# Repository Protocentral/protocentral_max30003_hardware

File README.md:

# ProtoCentral MAX30003 Single-lead ECG Breakout — Hardware

Open-source hardware design files for the **ProtoCentral MAX30003 Single-lead ECG Breakout**, built around the [Analog Devices (Maxim) MAX30003](https://www.analog.com/en/products/max30003.html), an ultra-low-power single-channel biopotential AFE with built-in R-to-R (heart-rate) detection.

The board takes a single ECG lead from a standard 3.5 mm electrode cable. It runs the MAX30003 from an on-board 1.8 V rail and translates the SPI and interrupt lines to your host's logic level, so it connects directly to 3.3 V or 5 V microcontrollers.

## Links

| | |
|---|---|
| 🛒 Product page | https://protocentral.com/product/protocentral-max30003-single-lead-ecg-breakout-board-v2/ |
| 💻 Arduino library | https://github.com/Protocentral/protocentral_max30003 |
| 📄 IC datasheet (Analog Devices / Maxim) | https://www.analog.com/media/en/technical-documentation/data-sheets/max30003.pdf |

## Specifications (v3)

- **AFE:** MAX30003 single-channel ECG front end with R-to-R detection
- **Electrode input:** 3.5 mm jack (Tip = ECGN, Ring = ECGP, Sleeve = VCM), 49.9 kΩ series resistors and an RC EMI filter on each input
- **Interface:** SPI (`CSB`, `SCLK`, `MOSI`, `MISO`) plus `INTB` / `INT2B` interrupts, level-translated to host `VCC` by a TXB0108
- **Clock:** on-board SiT1533 32.768 kHz oscillator driving `FCLK`
- **Supply:** 3.3 V – 5 V on `VCC`; on-board AP2112K-1.8 LDO for the AFE
- **Host header (J2, 8-pin):** 1 `INTB` · 2 `INT2B` · 3 `MISO` · 4 `MOSI` · 5 `SCLK` · 6 `CSB` · 7 `VCC` · 8 `GND`
- **Board:** 33.0 × 28.6 mm, 2-layer

## Revisions

| Revision | Design files | Notes |
|---|---|---|
| **v3** (current) | [`hardware/`](hardware/) | KiCad 10 redesign; [schematic PDF](hardware/protocentral-max30003-v3-schematic.pdf) |
| v2.0 | [`hardware/previous-revisions/v2.0/`](hardware/previous-revisions/v2.0/) | Eagle (2018) |
| v1.1 | [`hardware/previous-revisions/v1.1/`](hardware/previous-revisions/v1.1/) | Eagle (2017) |
| v1.0 | [`hardware/previous-revisions/v1.0/`](hardware/previous-revisions/v1.0/) | Eagle (2017) |

The v2.0 files also remain in the original [protocentral_max30003](https://github.com/Protocentral/protocentral_max30003/tree/master/hardware) repository, so existing links keep working.

## Repository layout

| Folder | Contents |
|---|---|
| [`hardware/`](hardware/) | v3 KiCad project (schematic + PCB layout) and the exported [schematic PDF](hardware/protocentral-max30003-v3-schematic.pdf) |
| [`hardware/previous-revisions/`](hardware/previous-revisions/) | Eagle design files for v1.0, v1.1 and v2.0, kept for reference |

## Important notice

This device is intended for research, education, and evaluation use only. It is **not** a medical diagnostic instrument and is not FDA, CE, or FCC approved for consumer use.

## License

The hardware design files in this repository are licensed under the **CERN Open Hardware Licence Version 2 – Permissive (CERN-OHL-P v2)**. See [LICENSE](LICENSE).

The accompanying Arduino library (in the separate [protocentral_max30003](https://github.com/Protocentral/protocentral_max30003) repository) is licensed under the MIT License.

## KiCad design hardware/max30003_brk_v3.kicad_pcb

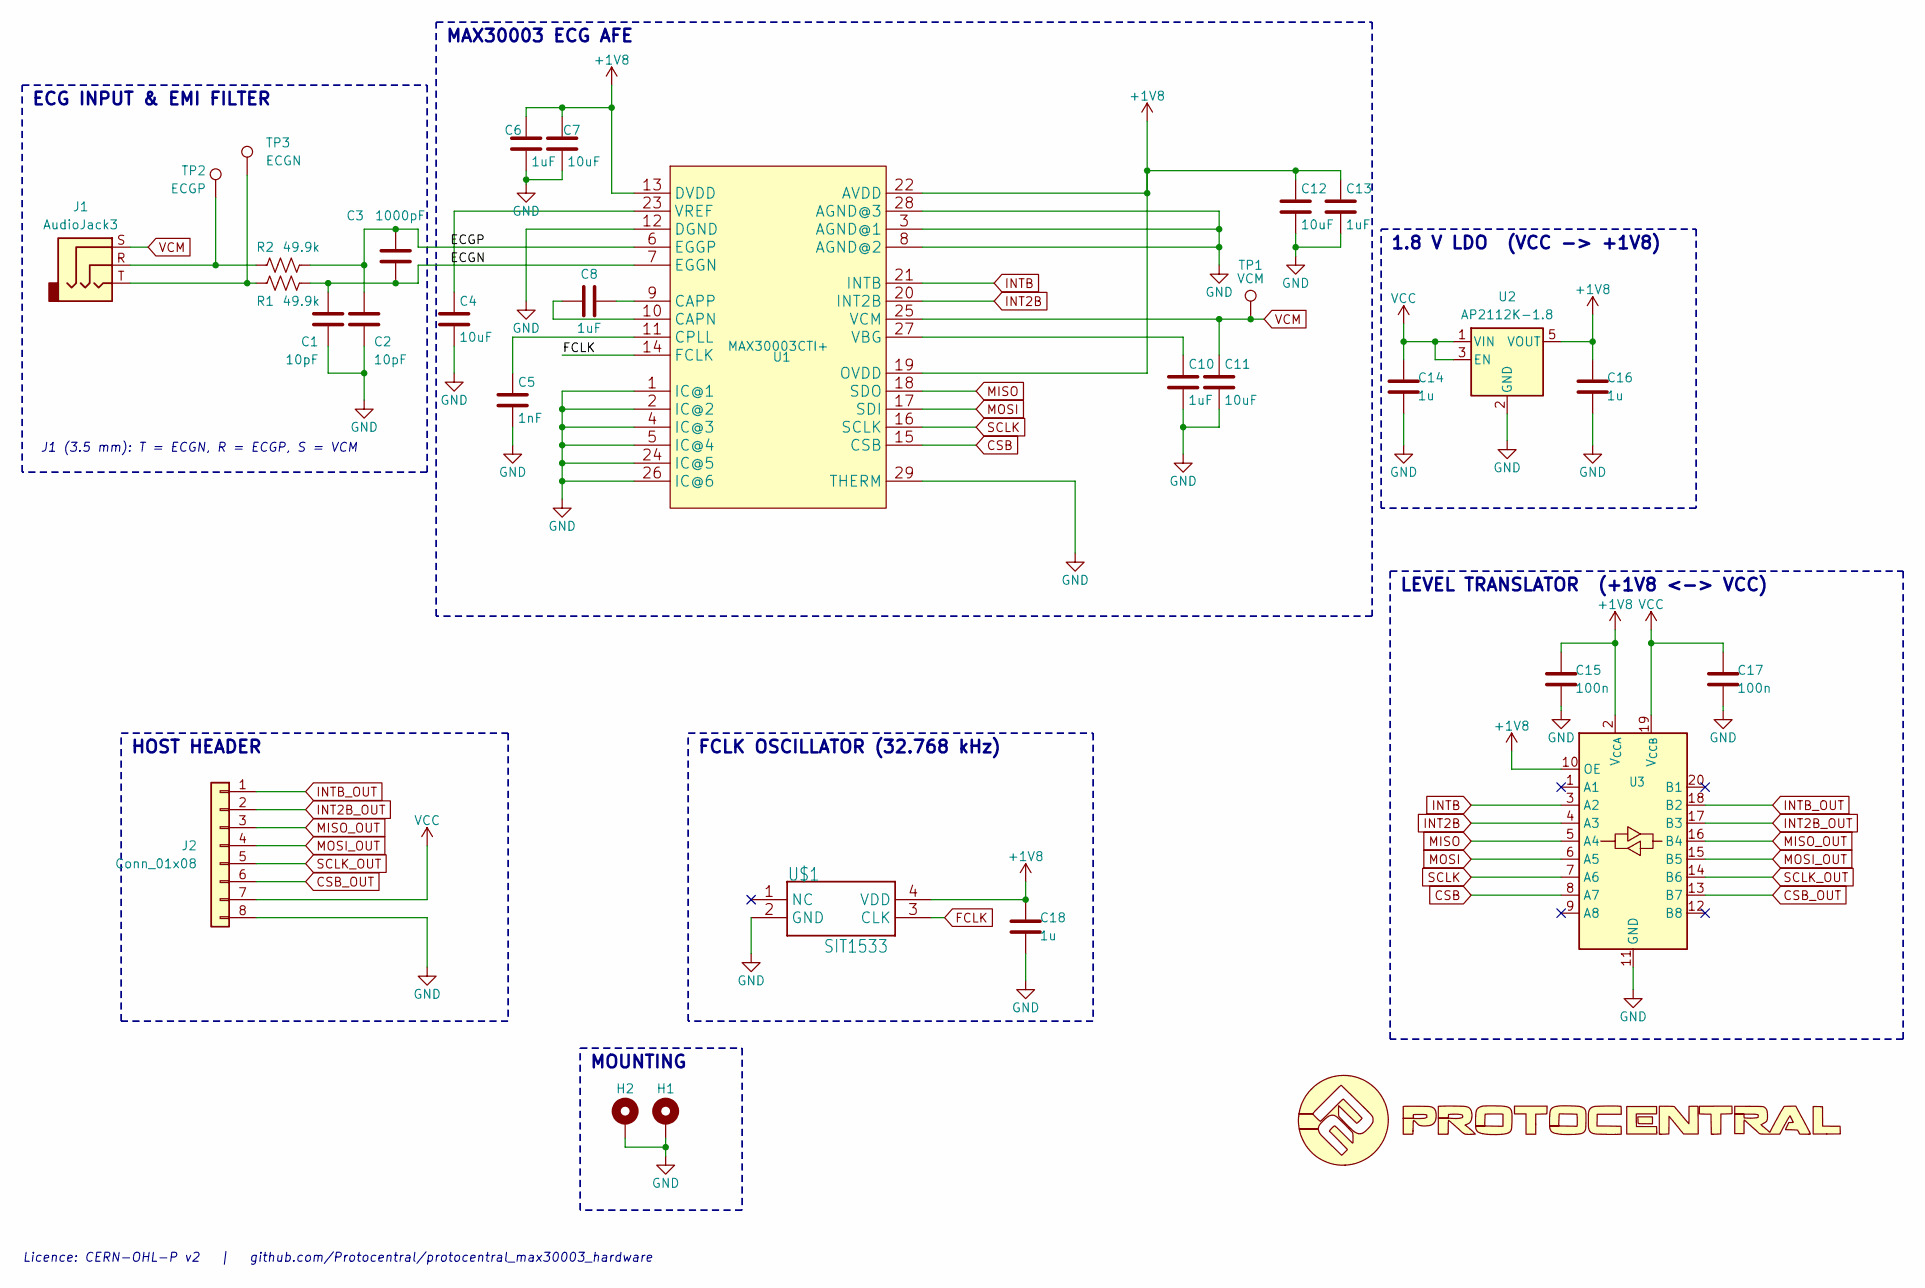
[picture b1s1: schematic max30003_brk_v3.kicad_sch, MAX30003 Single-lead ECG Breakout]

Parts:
C1, C2: 10pF; C_0402_1005Metric
C3: 1000pF; C_0402_1005Metric
C4: 10uF; C_0402_1005Metric
C5: 1nF; C_0402_1005Metric
C6, C8, C10, C13: 1uF; C_0402_1005Metric
C7, C11, C12: 10uF; C_0805_2012Metric
C14, C16, C18: 1u; C_0402_1005Metric
C15, C17: 100n; C_0402_1005Metric
H1, H2: MountingHole_Pad; MountingHole_2.2mm_M2_DIN965_Pad_TopBottom
J1: AudioJack3; Jack_3.5mm_CUI_SJ-3523-SMT_Horizontal
J2: Conn_01x08; PinHeader_1x08_P2.54mm_Vertical
R1, R2: 49.9k; R_0402_1005Metric
TP1: VCM; TestPoint_Pad_1.0x1.0mm
TP2: ECGP; TestPoint_Pad_1.0x1.0mm
TP3: ECGN; TestPoint_Pad_1.0x1.0mm
U1: MAX30003CTI+; QFN-28-1EP_5x5mm_P0.5mm_EP2.7x2.7mm
U2: AP2112K-1.8; SOT-23-5
U3: TXB0108PWR; TSSOP-20_4.4x6.5mm_P0.65mm
U4: LOGO
U$1: SIT1533; SiT1533_SIT

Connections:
+1V8: C6.1, C7.1, C12.1, C13.1, C15.2, C16.2, C18.2, U1.13 (DVDD), U1.19 (OVDD), U1.22 (AVDD), U2.5 (VOUT), U3.2 (V_{CCA}), U3.10 (OE), U$1.4 (VDD)
/ECGN: C1.1, C3.2, R1.2, U1.7 (EGGN)
/ECGP: C2.1, C3.1, R2.2, U1.6 (EGGP)
CSB: U1.15 (CSB), U3.8 (A7)
CSB_OUT: J2.6, U3.13 (B7)
FCLK: U1.14 (FCLK), U$1.3 (CLK)
GND: C1.2, C2.2, C4.2, C5.2, C6.2, C7.2, C10.2, C11.2, C12.2, C13.2, C14.1, C15.1, C16.1, C17.1, C18.1, H1.1 (1_1), H2.1 (1_1), J2.8, U1.1 (IC@1), U1.2 (IC@2), U1.3 (AGND@1), U1.4 (IC@3), U1.5 (IC@4), U1.8 (AGND@2), U1.12 (DGND), U1.24 (IC@5), U1.26 (IC@6), U1.28 (AGND@3), U1.29 (THERM), U2.2 (GND), U3.11 (GND), U$1.2 (GND)
INT2B: U1.20 (INT2B), U3.4 (A3)
INT2B_OUT: J2.2, U3.17 (B3)
INTB: U1.21 (INTB), U3.3 (A2)
INTB_OUT: J2.1, U3.18 (B2)
MISO: U1.18 (SDO), U3.5 (A4)
MISO_OUT: J2.3, U3.16 (B4)
MOSI: U1.17 (SDI), U3.6 (A5)
MOSI_OUT: J2.4, U3.15 (B5)
unnamed: J1.R, R2.1, TP2.1 (1_1)
unnamed: J1.T, R1.1, TP3.1 (1_1)
unnamed: C8.2, U1.10 (CAPN)
unnamed: C8.1, U1.9 (CAPP)
unnamed: C5.1, U1.11 (CPLL)
unnamed: C10.1, U1.27 (VBG)
unnamed: C4.1, U1.23 (VREF)
SCLK: U1.16 (SCLK), U3.7 (A6)
SCLK_OUT: J2.5, U3.14 (B6)
VCC: C14.2, C17.2, J2.7, U2.1 (VIN), U2.3 (EN), U3.19 (V_{CCB})
VCM: C11.1, J1.S, TP1.1 (1_1), U1.25 (VCM)

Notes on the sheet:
ECG INPUT & EMI FILTER
MAX30003 ECG AFE
1.8 V LDO (VCC -> +1V8)
HOST HEADER
FCLK OSCILLATOR (32.768 kHz)
LEVEL TRANSLATOR (+1V8 <-> VCC)
MOUNTING
J1 (3.5 mm): T = ECGN, R = ECGP, S = VCM
Licence: CERN-OHL-P v2 | github.com/Protocentral/protocentral_max30003_hardware

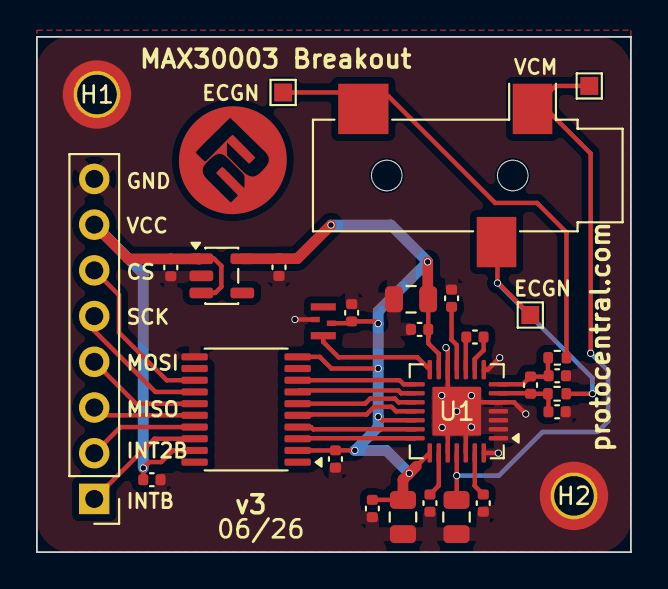
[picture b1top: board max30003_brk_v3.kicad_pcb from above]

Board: 2 copper layers, 33.0 x 28.6 mm, 30 parts (0 on the bottom side), 26 nets.
